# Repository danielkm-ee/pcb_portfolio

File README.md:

# PCB Portfolio
PCB designs I do in my free time, thanks for looking.

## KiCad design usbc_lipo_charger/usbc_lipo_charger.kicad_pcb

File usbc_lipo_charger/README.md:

# Battery Control Module Board
Uses a battery controller IC to charge lithium ion batteries using a USB C
port.

## Specifications
- Supports USB-C charging, 5V 3A
- Charges single cell, 3.7V lithium ion batteries
- Overvoltage and overcurrent protections for USB port

## Emphasis
- Low cost
- Small profile
- Minimal design

## Schematic
<object data="usbc_lipo_charger_schematic.pdf" type="application/pdf" width="600" height="800">
  <p> view/download pdf here: <a href="usbc_lipo_charger_schematic.pdf">Download PDF</a>.</p>
</object>

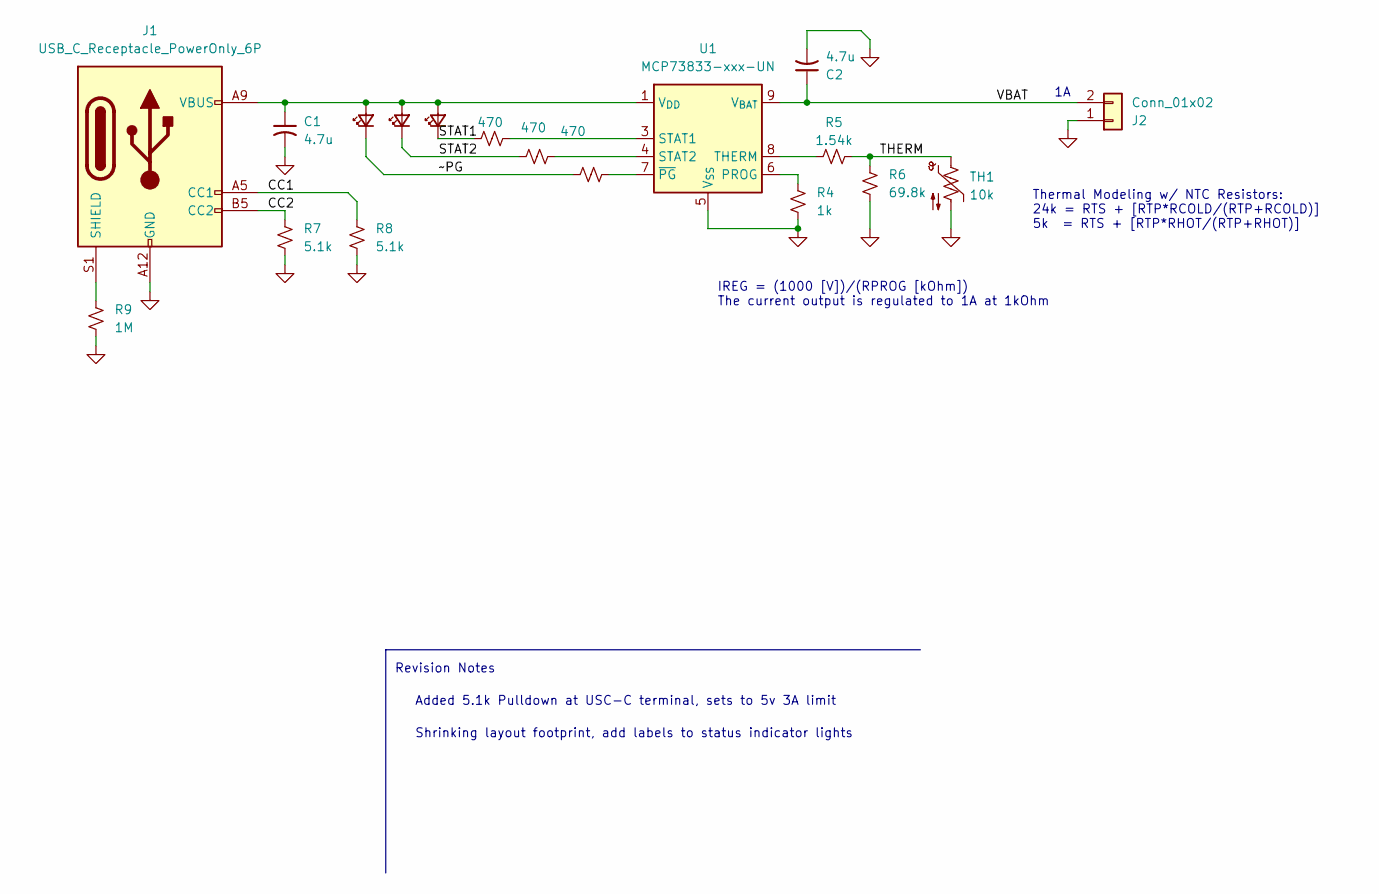
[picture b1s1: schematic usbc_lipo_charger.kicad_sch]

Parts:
C1, C2: 4.7u; C_0603_1608Metric
D1, D2, D3: LED; LED_0603_1608Metric
J1: USB_C_Receptacle_PowerOnly_6P; USB_TypeC_2171750001_MOL
J2: Conn_01x02; Molex_SPOX_5268-02A_1x02_P2.50mm_Horizontal
R1, R2, R3: 470; R_0603_1608Metric
R4: 1k; R_0603_1608Metric
R5: 1.54k; R_0603_1608Metric
R6: 69.8k; R_0603_1608Metric
R7, R8: 5.1k; R_0603_1608Metric
R9: 1M; R_0603_1608Metric
TH1: 10k; R_0603_1608Metric
U1: MCP73833-xxx-UN; MSOP-10_3x3mm_P0.5mm

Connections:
/CC1: J1.A5 (CC1), R8.1
/CC2: J1.B5 (CC2), R7.1
/STAT1: D3.1 (K), R1.1
/STAT2: D2.1 (K), R2.1
/THERM: R5.2, R6.1, TH1.1
/VBAT: C2.1, J2.2, U1.9 (V_{BAT}), U1.10 (V_{BAT})
/~PG: D1.1 (K), R3.1
GND: C1.2, C2.2, J1.A12 (GND), J1.B12 (GND), J2.1, R4.2, R6.2, R7.2, R8.2, R9.2, TH1.2, U1.5 (V_{SS})
unnamed: C1.1, D1.2 (A), D2.2 (A), D3.2 (A), J1.A9 (VBUS), J1.B9 (VBUS), U1.1 (V_{DD}), U1.2 (V_{DD})
unnamed: J1.S1 (SHIELD), R9.1
unnamed: R4.1, U1.6 (PROG)
unnamed: R1.2, U1.3 (STAT1)
unnamed: R2.2, U1.4 (STAT2)
unnamed: R5.1, U1.8 (THERM)
unnamed: R3.2, U1.7 (~PG)

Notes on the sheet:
Shrinking layout footprint, add labels to status indicator lights
Revision Notes
Thermal Modeling w/ NTC Resistors: 24k = RTS + [RTP*RCOLD/(RTP+RCOLD)] 5k = RTS + [RTP*RHOT/(RTP+RHOT)]
IREG = (1000 [V])/(RPROG [kOhm]) The current output is regulated to 1A at 1kOhm
Added 5.1k Pulldown at USC-C terminal, sets to 5v 3A limit

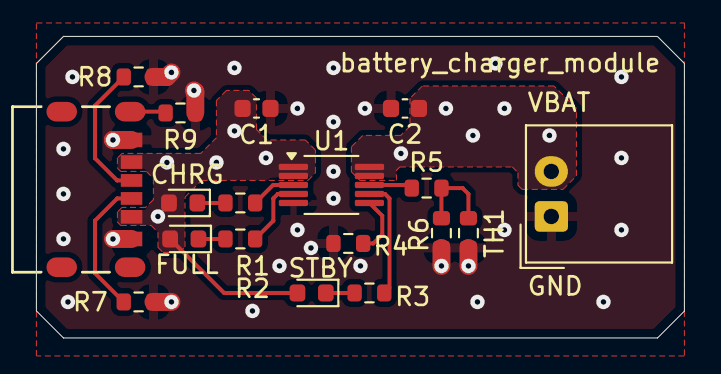
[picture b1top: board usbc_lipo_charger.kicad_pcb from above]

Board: 2 copper layers, 36.0 x 16.8 mm, 18 parts (0 on the bottom side), 15 nets.

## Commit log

2025-06-23 initial commit, add lipo charger
2025-06-23 adding comments
2025-06-23 revision 1, make smaller, add pcb heatsinking, label status leds
2025-06-23 make readme
2025-06-23 add images to lipo charger readme
2025-06-23 update lipo charger readme
2025-06-23 fix typo in readme
2025-06-28 add dorji_radio project
2025-06-28 add power input for battery
2025-07-04 add groundplane on front copper of pcb
2025-07-04 update pcb image, meet manufacture requirements
2025-07-04 add gitignore
